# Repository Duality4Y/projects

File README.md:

projects
========

geany projects

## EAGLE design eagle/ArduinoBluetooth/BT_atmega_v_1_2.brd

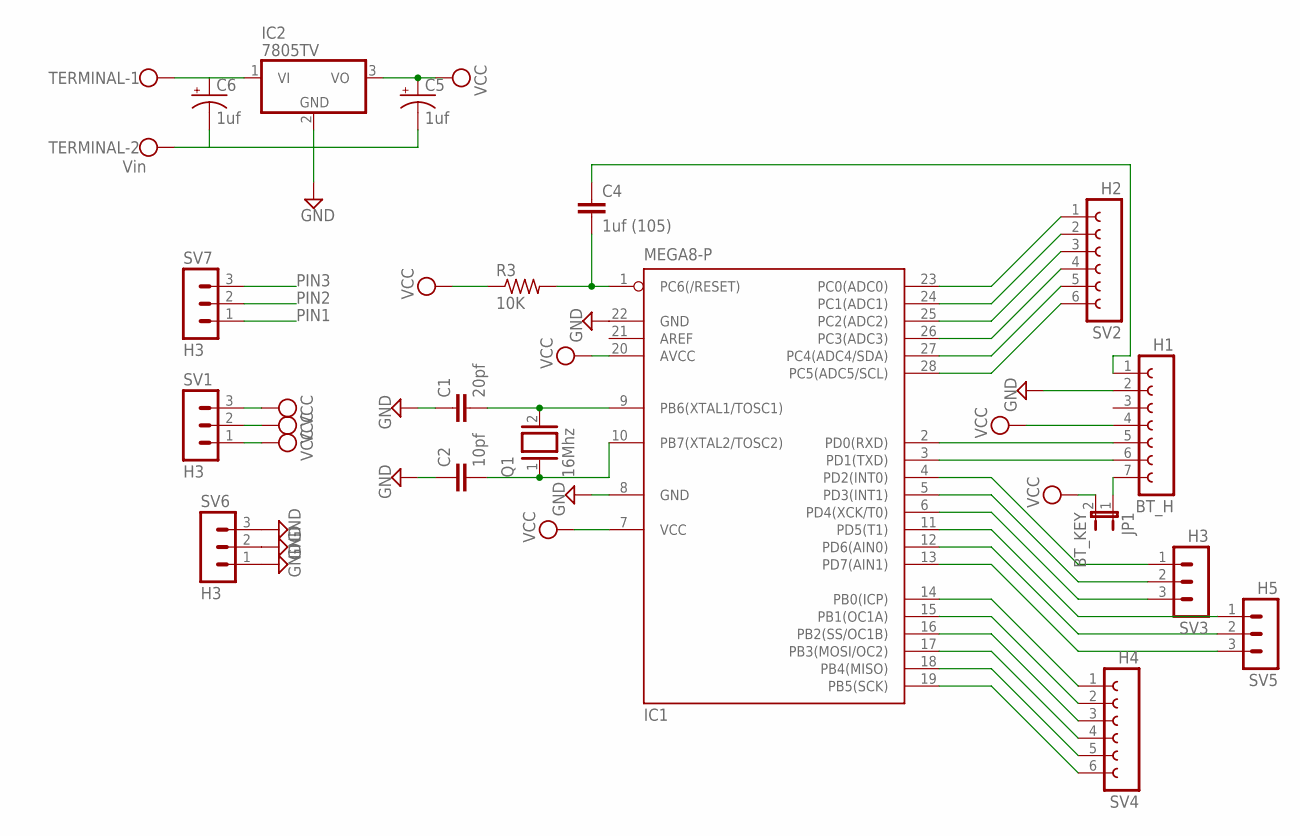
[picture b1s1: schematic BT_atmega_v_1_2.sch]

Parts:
BT_H: H1; FE07
C1: 20pf; C2.5-2
C2: 10pf; C2.5-2
C4: 1uf (105); C2.5-2
C5, C6: 1uf; E5-4
IC1: MEGA8-P; DIL28-3
IC2: 7805TV; TO220V
JP1: BT_KEY; JP1
Q1: 16Mhz; QS
R3: 10K; 0204/5
SV1, SV3, SV6, SV7: H3; MA03-1
SV2: H2; FE06
SV4: H4; FE06
SV5: H5; MA03-1
TERMINAL: Vin; W237-102

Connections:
GND: BT_H.2, C1.1, C2.1, C5.-, C6.-, IC1.8 (GND), IC1.22 (GND), IC2.2 (GND), SV6.1, SV6.2, SV6.3, TERMINAL.2
unnamed: C1.2, IC1.9 (PB6(XTAL1/TOSC1)), Q1.2
unnamed: C2.2, IC1.10 (PB7(XTAL2/TOSC2)), Q1.1
unnamed: BT_H.7, JP1.1
unnamed: IC1.23 (PC0(ADC0)), SV2.1
unnamed: IC1.24 (PC1(ADC1)), SV2.2
unnamed: IC1.25 (PC2(ADC2)), SV2.3
unnamed: IC1.26 (PC3(ADC3)), SV2.4
unnamed: IC1.27 (PC4(ADC4/SDA)), SV2.5
unnamed: IC1.28 (PC5(ADC5/SCL)), SV2.6
unnamed: IC1.4 (PD2(INT0)), SV3.1
unnamed: IC1.5 (PD3(INT1)), SV3.2
unnamed: IC1.6 (PD4(XCK/T0)), SV3.3
unnamed: IC1.11 (PD5(T1)), SV5.1
unnamed: IC1.12 (PD6(AIN0)), SV5.2
unnamed: IC1.13 (PD7(AIN1)), SV5.3
unnamed: IC1.14 (PB0(ICP)), SV4.1
unnamed: IC1.15 (PB1(OC1A)), SV4.2
unnamed: IC1.16 (PB2(SS/OC1B)), SV4.3
unnamed: IC1.17 (PB3(MOSI/OC2)), SV4.4
unnamed: IC1.18 (PB4(MISO)), SV4.5
unnamed: IC1.19 (PB5(SCK)), SV4.6
unnamed: BT_H.1, C4.1
unnamed: C6.+, IC2.1 (VI), TERMINAL.1
PIN1: C4.2, IC1.1 (PC6(/RESET)), R3.2, SV7.1
PIN2: BT_H.5, IC1.2 (PD0(RXD)), SV7.2
PIN3: BT_H.6, IC1.3 (PD1(TXD)), SV7.3
VCC: BT_H.4, C5.+, IC1.7 (VCC), IC1.20 (AVCC), IC2.3 (VO), JP1.2, R3.1, SV1.1, SV1.2, SV1.3

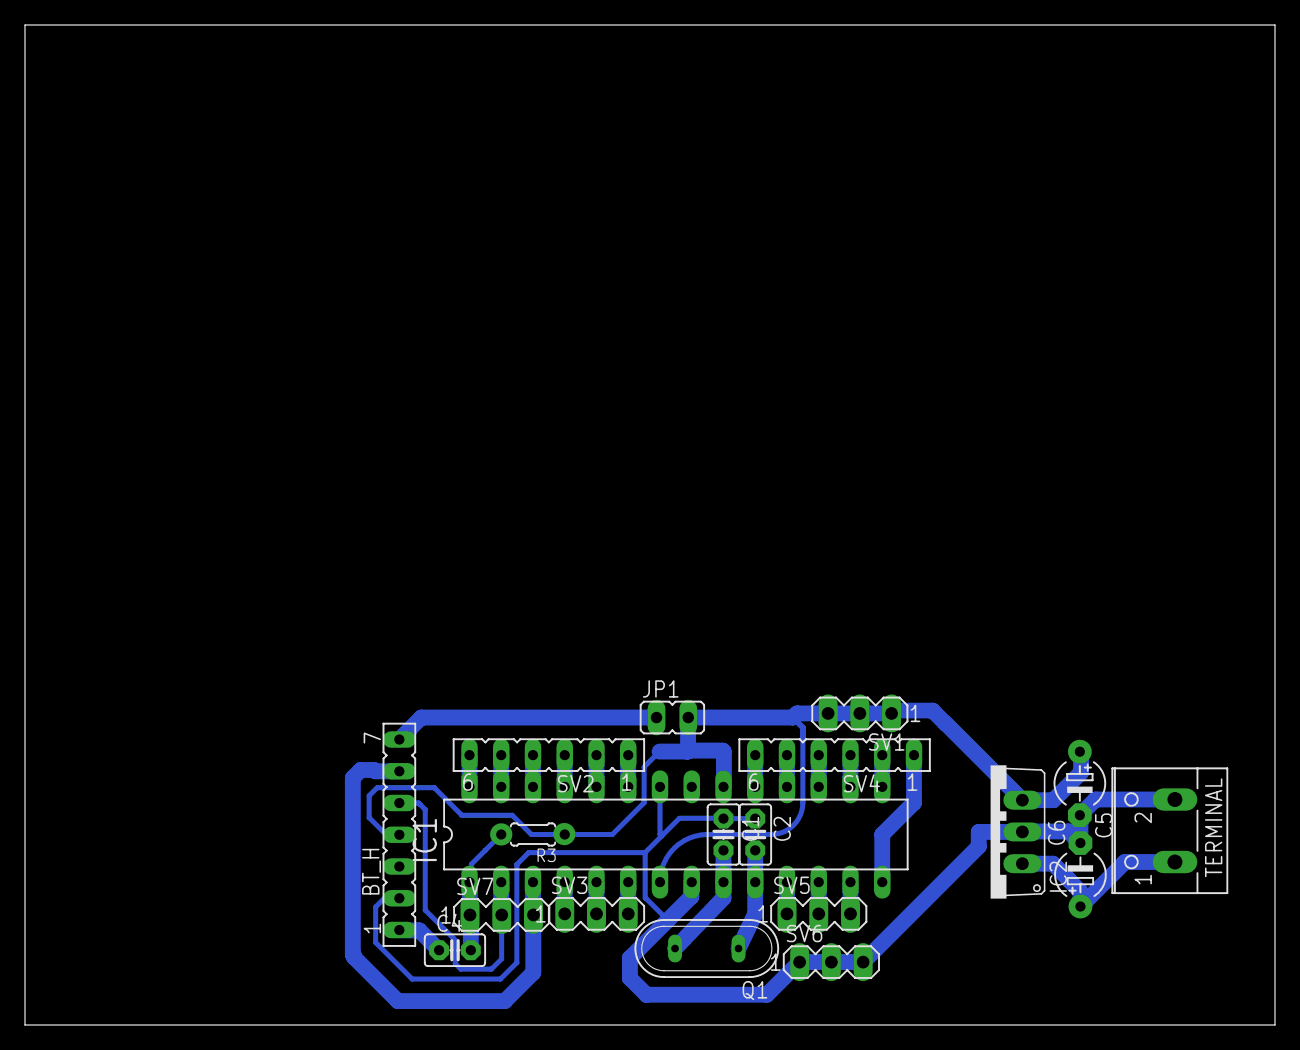
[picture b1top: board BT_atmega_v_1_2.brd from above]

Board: 2 copper layers, 100.0 x 80.0 mm, 19 parts (0 on the bottom side), 28 nets.

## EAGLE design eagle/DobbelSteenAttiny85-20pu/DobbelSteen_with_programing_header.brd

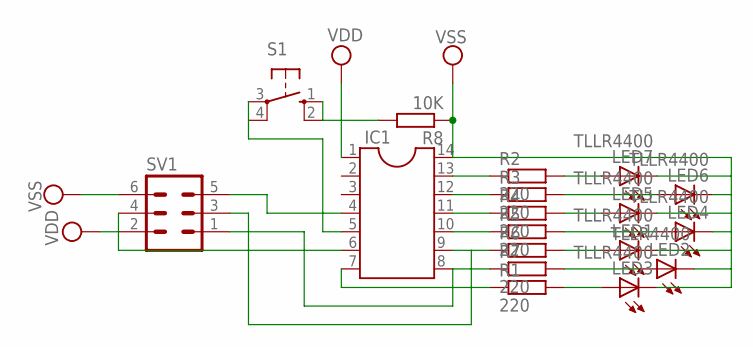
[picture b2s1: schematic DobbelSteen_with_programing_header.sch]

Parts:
IC1: DIL14S; SOCKET-14
LED1, LED2, LED3, LED4, LED5, LED6, LED7: TLLR4400; LED3MM
R1, R2, R3, R4, R5, R7: 220; 0204/7
R6: R0204/7; 0204/7
R8: 10K; 0204/7
S1: 10-XX; B3F-10XX
SV1: MA03-2

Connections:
unnamed: IC1.13, R2.1
unnamed: IC1.12, R3.1
unnamed: IC1.11, R4.1
unnamed: IC1.10, R5.1
unnamed: IC1.8, R7.1, SV1.1
unnamed: IC1.7, R1.1
unnamed: LED7.A, R2.2
unnamed: LED6.A, R3.2
unnamed: LED5.A, R4.2
unnamed: LED4.A, R5.2
unnamed: LED1.A, R6.2
unnamed: LED2.A, R7.2
unnamed: LED3.A, R1.2
unnamed: IC1.6, SV1.4
unnamed: R8.2, S1.1 (S), S1.2 (S1)
unnamed: IC1.5, S1.3, S1.4 (P1)
unnamed: IC1.4, SV1.5
unnamed: IC1.9, R6.1, SV1.3
VDD: IC1.1, SV1.2
VSS: IC1.14, LED1.K (C), LED2.K (C), LED3.K (C), LED4.K (C), LED5.K (C), LED6.K (C), LED7.K (C), R8.1, SV1.6

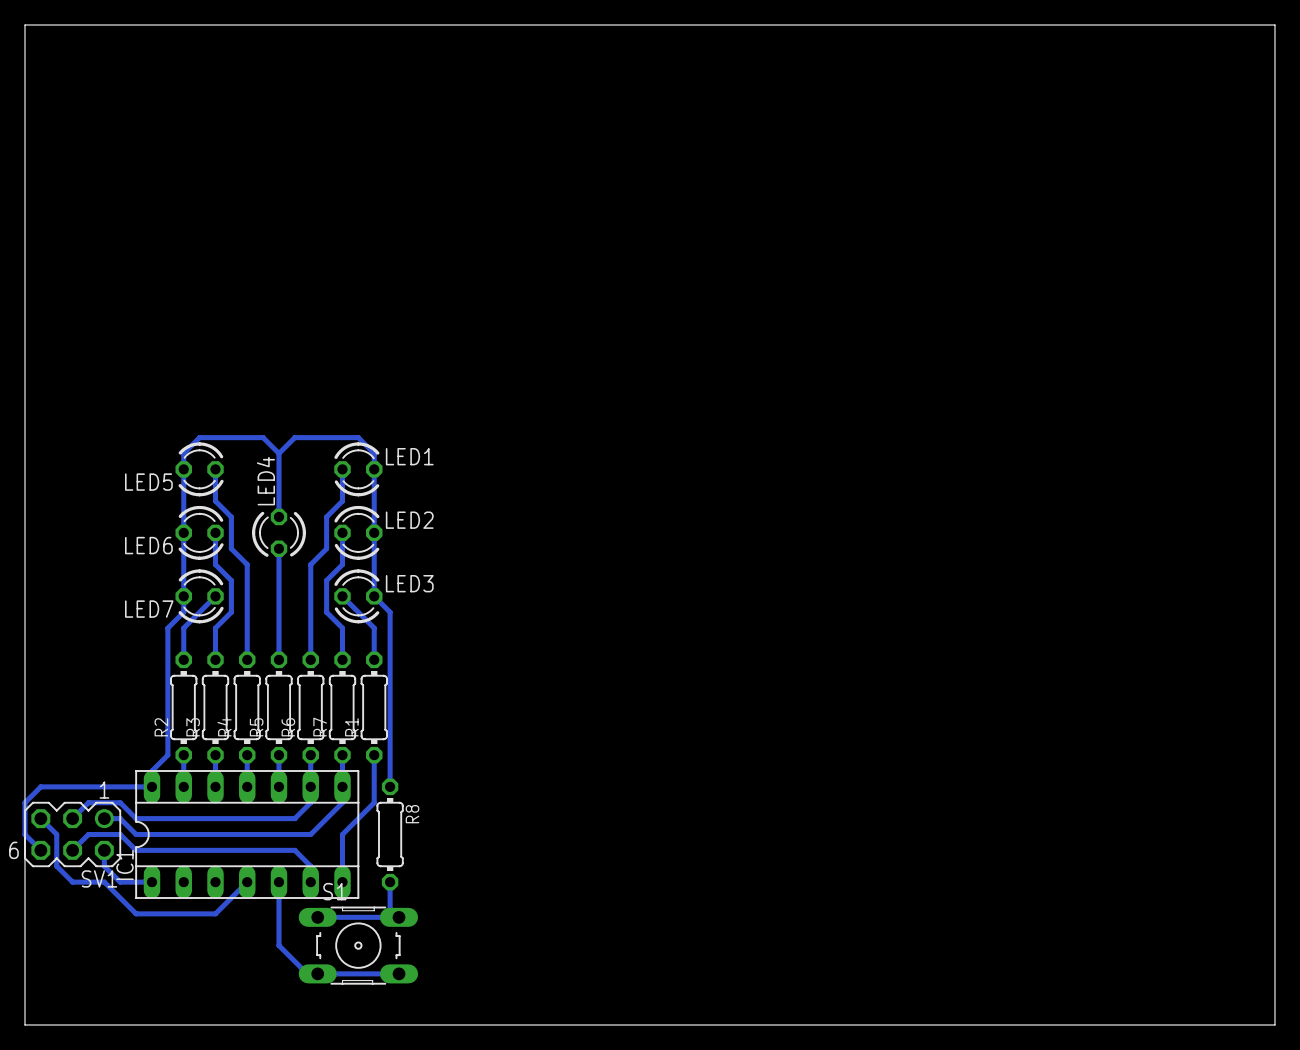
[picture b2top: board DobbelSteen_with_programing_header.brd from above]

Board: 2 copper layers, 100.0 x 80.0 mm, 18 parts (0 on the bottom side), 20 nets.

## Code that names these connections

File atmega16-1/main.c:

#define F_CPU 20000000
#include <avr/io.h>
#include <avr/interrupt.h>
#include <util/delay.h>
#include "uart.cpp"
/*
 * WE = PD5
 * OE = PD4
 * CE = PD3
 * */

#define WE_PIN				(PD5)
#define OE_PIN				(PD4)
#define CE_PIN				(PD3)
#define PIN_DDR				(DDRD)
#define PIN_PORT			(PORTD)

#define CONTROLE_OUTPUT		(PIN_DDR |= (1<<WE_PIN)|(1<<OE_PIN)|(1<<CE_PIN))
/*
 * becasue the controle lines are active low,
 * well meen by setting a pin pulling it low.
 * and clearing a pin setting that pin high.
 * */
#define SET_WE				(PIN_PORT &= ~(1<<WE_PIN))
#define CLEAR_WE			(PIN_PORT |= (1<<WE_PIN))
#define SET_OE				(PIN_PORT &= ~(1<<OE_PIN))
#define CLEAR_OE			(PIN_PORT |= (1<<OE_PIN))
#define SET_CE				(PIN_PORT &= ~(1<<CE_PIN))
#define CLEAR_CE			(PIN_PORT |= (1<<CE_PIN))

#define DATA_BUS_DDR		(DDRB)
#define DATA_BUS_PORT		(PORTB)
#define DATA_BUS_DPIN		(PINB)

#define DATA_BUS_INPUT		(DDRB = 0x00)
#define DATA_BUS_OUTPUT		(DDRB = 0xFF)
#define DATA_BUS_WRITE(X)	(PORTB = X)
#define DATA_BUS_READ		PINB

#define ADDR_BUS_A_DDR		(DDRA)
#define ADDR_BUS_B_DDR		(DDRC)
#define ADDR_BUS_C_DDR		(DDRD)

#define ADDR_BUS_A_PORT		(PORTA)
#define ADDR_BUS_B_PORT		(PORTC)
#define ADDR_BUS_C_PORT		(PORTD)

#define ADDR_BUS_A_DPIN		(PINA)
#define ADDR_BUS_B_DPIN		(PINC)
#define ADDR_BUS_C_DPIN		(PIND)

/*
 * make seperate inputs outputs for A,B,C
 * like addr_bus_a_input
 * addr_bus_b_input
 * and so on for write output and read.
 * make functions to do the coversion/calculations for
 * what part of the data goes where.
 * */

//#define ADDR_BUS_INPUT		do{(ADDR_BUS_A_DDR = ADDR_BUS_B_DDR = 0x00);(ADDR_BUS_C_DDR |= ( 1<<PD6)|( 1<<PD7));}while(0);
//#define ADDR_BUS_OUTPUT		do{(ADDR_BUS_A_DDR = ADDR_BUS_B_DDR = 0xFF);(ADDR_BUS_C_DDR &= ~( (1<<PD6)|(1<<PD7) ));}while(0);

//#define ADDR_BUS_WRITE(X)	do{(ADDR_BUS_A_PORT = (X&0xFF));(ADDR_BUS_B_PORT = (X&0xFF00));( ADDR_BUS_C_PORT = ( X&( ( 1<<PD6)|( 1<<PD7))));}while(0);
//#define ADDR_BUS_READ		(0x000000 | (ADDR_BUS_A_DPIN) | (ADDR_BUS_B_DPIN<<8) | (ADDR_BUS_C_DPIN&( ( 1<<PD6)|( 1<<PD7))<<16) )

//#define ADDR_BUS_WRITE(X)	(ADDR_BUS_A_PORT = X)
//#define ADDR_BUS_READ		(ADDR_BUS_A_PIN)

#define ADDR_BUS_A_INPUT	(ADDR_BUS_A_DDR = 0x00)
#define ADDR_BUS_B_INPUT	(ADDR_BUS_B_DDR = 0x00)
#define ADDR_BUS_C_INPUT	(ADDR_BUS_C_DDR &= ~((1<<PD6)|(1<<PD7)))

#define ADDR_BUS_A_OUTPUT	(ADDR_BUS_A_DDR = 0xFF)
#define ADDR_BUS_B_OUTPUT	(ADDR_BUS_B_DDR = 0xFF)
#define ADDR_BUS_C_OUTPUT	(ADDR_BUS_C_DDR |= (1<<PD6)|(1<<PD7))

#define ADDR_BUS_A_WRITE(X)
#define ADDR_BUS_B_WRITE(X)
#define ADDR_BUS_C_WRITE(X)

#define ADDR_BUS_A_READ
#define ADDR_BUS_B_READ
#define ADDR_BUS_C_READ

#define MANUFACTURER_ID



void init_flash_interface()
{
	DATA_BUS_INPUT;
	ADDR_BUS_A_INPUT;
	ADDR_BUS_B_INPUT;
	ADDR_BUS_C_INPUT;
	CONTROLE_OUTPUT;
	
	CLEAR_CE;
	CLEAR_OE;
	CLEAR_WE;
}

void writeAddress(uint32_t address)
{
	ADDR_BUS_A_WRITE(address&0xFF);
	ADDR_BUS_B_WRITE((address>>8)&0xFF);
	ADDR_BUS_C_WRITE((address>>16)&0xFF);
}

uint8_t read_flash(uint32_t address)
{
	DATA_BUS_INPUT;
	SET_CE;
	SET_OE;
	CLEAR_WE;
	ADDR_BUS_A_OUTPUT;
	ADDR_BUS_B_OUTPUT;
	ADDR_BUS_C_OUTPUT;
	//ADDR_BUS_WRITE(address);
	writeAddress(address);
	short readByte = DATA_BUS_READ;
	CLEAR_OE;
	CLEAR_CE;
	ADDR_BUS_A_INPUT;
	ADDR_BUS_B_INPUT;
	ADDR_BUS_C_INPUT;
	return readByte;
}
int main(void)
{
	init_uart();
	init_flash_interface();
	while(1)
	{
		unsigned long adder = 0;
		unsigned long limit = 0xFF;
		for(adder = 0;adder <= limit;adder++)
		{
			uart_putdata(read_flash(adder));
		}
		break;
	}
	return(0);
}

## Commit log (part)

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2013-11-15 this is the first commit of my projects folder, i keep my geany projects here.
2013-11-16 another commit
2013-11-16 more work on display atmega16 can now show text working on more
2013-11-19 this another commit
2013-11-20 this a commit, broken laptop :S
2013-11-21 worked on more code for display, tried setting address to write to on display, no progress made there yet, had to make a function for representing a binary number, so I could debug print it
2013-11-24 a commit
2013-11-25 made more discoveries today, it was a productive day
2013-11-27 this lol
2013-11-27 working game of life with DmDisplay code I wrote. Not going to change any more, its perfect it works (atmega16-3 folder)
2013-11-28 got serial working
2013-11-29 want to us i2c
2013-12-01 ds1621 folder is arduino sketch uses wire.h to comunicate with the chip, it is a temperature sensor.
2013-12-02 working on pwm. and timers
2013-12-03 working on debuging over serial for pwm ideas
2013-12-03 doing more pwm, not making any progress heregit add .
2013-12-05 ds1621 for school project
2013-12-11 worked on game of life.
2013-12-14 finally got it working writePixel() function nolonger overwrites any other pixels in the same display memory address.
2013-12-14 quick new function for clearing al markers. also this is pretty awesome that i got pixel writing working :)
2013-12-14 just a little commit
2013-12-15 can now draw lines circles and rectangles. plan on implementing a function for drawing arcs.
2013-12-15 worked on some circles more.
2013-12-16 did some clean up
2013-12-16 put/moved functions to DmDisplay library.
2013-12-18 made my dice work more reliable. when you shake it. it wil throw a number. but when you hold it still it won't.
2014-01-04 got game of life totally working! even oscilators work and gliders and space ships.
2014-01-06 created a way to reset the field by pushing a button
2014-01-07 put the 5x7 font into program memmory.
2014-01-07 game of life on pixel level was awesome, displayed a few flaws like the ram, (used a byte per cell) but you can easily fit 8 cels in a byte .. with some smart code, a grid of 15 by 15 pixels was abou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
2014-01-08 just a commit for store, also implementing a rounded edge rectangle functions is pretty hard.
2014-01-12 added a way to work on avr assembly.
2014-01-12 precious commit
2014-01-14 worked on some avr assembly
2014-01-19 got a dice working in avr assembly :) so happy!
2014-01-20 just a commit
2014-01-27 worked on assembly
2014-01-28 worked on rounded edges some more. but giving up on that for the moment.
2014-01-28 worked some more on game of life.
2014-02-10 worked some more game of life in python :)
2014-02-10 worked some more on game of life in python
2014-02-10 created some colors
2014-02-10 did some clearing up the colors
2014-02-12 work on game of life some more,
2014-02-13 worked on Calculator2.java
2014-02-20 worked on implementig computer logic in python all ones and zero's see main.py for testing routine
2014-03-02 my eagle files they are importent to me :)
2014-03-02 more eagle file added
2014-03-04 worked on multiplexing with shift registers.
2014-03-04 worked on vault freaking register not working with my code.
2014-03-10 a backup of the safe software just to be sure :)
2014-03-11 worked on safe fixed uart
2014-03-11 worked on safe, worked on parsing commands
2014-03-11 worked on authenticating and a menu of sorts with commands. the basic frame works. besides still need to add servo moving capability.
2014-03-15 worked on servo controle and got that working. not totally like it should though
2014-03-16 got non blocking screen working, also able to keep time, in seconds though
2014-03-18 worked on rules that serial comm has to listen to.
2014-03-19 worked on servo code, now able to put the servo on any pin you like. all there is left to be done now is work on the main program, the basic skeleton is there. won't take much work now :)
2014-03-20 worked on transient recorder
2014-03-21 just a backup commit
2014-03-22 worked on servo code, this thing is giving me headaches. anyway implementing the new command system partialy
2014-03-26 login in acces working through serial.
2014-03-26 alot of stuff is done
2014-03-27 worked on implementing stuff
2014-04-01 worked on CarApplet.java
2014-04-01 worked on TellerApplet.java
2014-04-08 got display uart and servo to work together, being able to login reliably now
2014-04-08 worked on CarAppletTurning.java
2014-04-10 can draw a car, and got rotating wheels working :)
2014-04-10 worked on dobbelSteenTester.java
2014-04-11 worked on CarAppletTurning2.java
2014-04-24 backup commit
2014-05-13 worked on timers kinda got it working.
2014-05-20 worked on assembly and got blink led withtimer overflow working and compare and interrupts.
2014-06-06 bug fixing how much fun
2014-06-09 there was a 'memory leak' when the bits[] and data[] array were declared outside the function that used them. when moving these arrays in the function fixed the seg faults i kept getting.
2014-06-09 worked on getting date and sensor input
2014-06-10 my spi api works! I am using it to read out a mcp3208 adc 12bit. and that works fine. finaly!
2014-06-10 modified: WeatherStation/libs/spi.h
2014-06-13 worked on adc code, making it more portable.
2014-06-13 worked on adc definitions some more.
2014-06-16 got spi.c compiling properly git add .
2014-06-16 worked on lots of stuf adc works dht11 works. almost got it passing it into the .csv files
2014-06-17 could stop working, worked on spewing out csv files, almost there anyway.
2014-06-18 my software works. the sensors can be read with the pi, and data will be stored in the .csv files.
2014-06-19 updating the databases, collected data for testing.
2014-06-20 update database
2014-06-23 a merg database updates. and some javacode
2014-06-24 database update
2014-06-28 data base update
2014-07-08 worked on multiplexing bus interface for interfacing to ram.
2014-08-05 just working on a game again :D
2014-08-12 worked on the game more nothing real working yet
2014-08-13 worked on lots of stuff, threw it all out of the window (collision detection didn't work so great, and other stuff i'll redo
2014-08-26 worked on collsions with tiles. still verry verry buggy.
2014-09-11 worked on the flash chip interface, more tricky that i initialy thought.
2014-09-15 just committing worked on my game some more
2014-09-16 still collission detection and acting on them is still tricky
2014-09-16 still can't get it to work really
2014-09-20 why must it be so tricky. the collision detection is not the problem. but putting the box where it collided is though.
2014-09-22 worked on x86 assembly, this hex printing is really hard to do
2014-09-23 working on printing hex in x86 assembly, feels like i am getting close but not yet, got a weird bug, where it prints 13 chars further. but i feel like i can solve that though.
2014-09-30 worked on some c code interpreter thing
2014-10-02 worked on the calculator stack thing. don't really have it working, but i have some ideas. like walking down a percedence list. and stuff like that. but first make it work for +-/* and then all the o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
2014-10-02 got it working better now the interpreter. it interprets + - and numbers and pushes them on the apropriate stacks and such. and these are only the parsing parts yet. still have to do the processing p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
2014-10-04 worked on the calculator fixed some bugs. made some new bugs :D for example: entering -5+-1+1-5 puts -5 -1 1 -5 on the value stack and + + on the operator stack. oh wait it might have something to do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
2014-10-04 just a quick commit, 1-1 works 1-5 works 1+-1 works -1 works
2014-10-05 worked on calculator more, had a problem with entering a number minus another the result would be switched. but i figure out what went wrong like the left value was loaded first instead of the right 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
2014-10-06 i keep on learning about pointers, i hope one day to solidify my knowledge on them though ..
2014-10-06 worked on calculator seems like processing of the data (to do calculations ) hapens backward example 10*1000/40 should do 10*1000 and after that 10000/40. but my calculator does 1000/40 and after tha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
2014-10-15 worked on arduino wifi esp module got that working! , also did some c program cleaning
2014-10-16 worked on my c code some more. putting up a token frame work. building a lexer. after that a parzer. and who know what will happen
2014-10-17 worked on something a little more
2014-10-17 worked on code got carried away. fun working with the wifi module!
2014-10-18 worked on learning c a bit better. you can always learn more !
2014-10-21 worked on serial module stuff
2014-10-22 worked on learning c the hard way. looks really interesting near then end of the bookgit add . although i know my C this book is still verry usefull. and teaches me alot. i am following it instructio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
2014-10-25 been workig on the c learning thing.
2014-10-25 learned alot struct pointer databases ow yea!
2014-10-26 doing: http://c.learncodethehardway.org/book/ex18.html and learning from it. strange order is ... strange
2014-10-27 tricky stuff with c building an object system, but i think i understand how the underlying code works. and that should be the goal right ?
2014-10-27 worked a little game in c (for the book) and it works. so the object system implemented in c works!
2014-10-28 learned lots! duff's device and such, never use it!
2014-10-29 exercise 24 never use scanf()
2014-10-29 learned lots on variable length input. also the exercise (25) in the book worked, but when it asked for a initial I entered R. as is normal here. but it broke the through fall. but turns out fgetc();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
2014-10-30 just a commit. worked on the book halve way through making first real program
2014-10-31 worked on the c code a bit more. db.c is done now. couldn't get apr to compile, turns out were typo's so yea.
2014-11-01 worked on the real program thing more. and boy big project :D already taking me 3 days. and i don't know how much longer it's going to take ..
2014-11-02 worked on shell.c taking me a long time to do exercise 26 ..
2014-11-03 learning lots on make files!
2014-11-04 alright worked some more on this python game thing. now use dx dy to determine which side of a tile or box i hit and respond acordingly to that. hope i get it working.
2014-11-05 worked on that game some more, it's giving me lots of trouble and i can't find any good sources on what i need.
2014-11-06 got a rect moving in a circlegit add -A!
2014-11-10 worked on some pygame code
2014-11-12 worked on lcd matrix software got it working !
2014-11-12 got led matrix working. maked seperate souces. and now go for that led cube :)
2014-11-13 worked on coding and finding a nice font can't get it to work.
2014-11-15 this is a commit
2014-11-16 ok i have my led matrix working and a python script that leds me draw anything on that ledmatrix !
2014-11-17 commented lots in displaySerial.py, pushed up the baudrate, have a bug where wrong pixels are drawn, or atleast all with an offset. leftmouse and holding draws, rightmousebutton and holding erases pi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
2014-11-18 got a mouse displaying working! nice and fun maybe i'll make some games for it. like a snake controlled by mouse ! or or keyboard! oh yea!
2014-11-19 working on a library of sorts it's not there yet. but maybe it wil making deving easier. or atleast make fun application making easier (python script) C code hasn't changed
2014-11-25 worked on python scripts. workd on the python module i am writing. it's good fun, have been working on the demo, made a skeleton to fill in for later. made SDLM class not crash on error. but simply r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
2014-11-28 I made it easier to run patterns in python scripts for the art-net. code based upon aprogas his art-net python code. I added a -c or -config switch that defaults to default_conf.py which broadcasts. 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
2014-11-29 ok that whole loading system works ! i've been deving a pattern of falling rain. the original implementation didn't work for the ledmatrix. because it was for the ohm2013 ledpoles. they were wired di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
2014-11-29 worked alot of things out made a readme ! do definitly read ! made lots readable. made runPatternJob.py catch ctrl-C to be sure things are closed if interupted.
2014-12-12 removed something
